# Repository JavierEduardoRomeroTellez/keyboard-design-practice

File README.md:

# keyboard-design-practice
 Practicing keyboard design

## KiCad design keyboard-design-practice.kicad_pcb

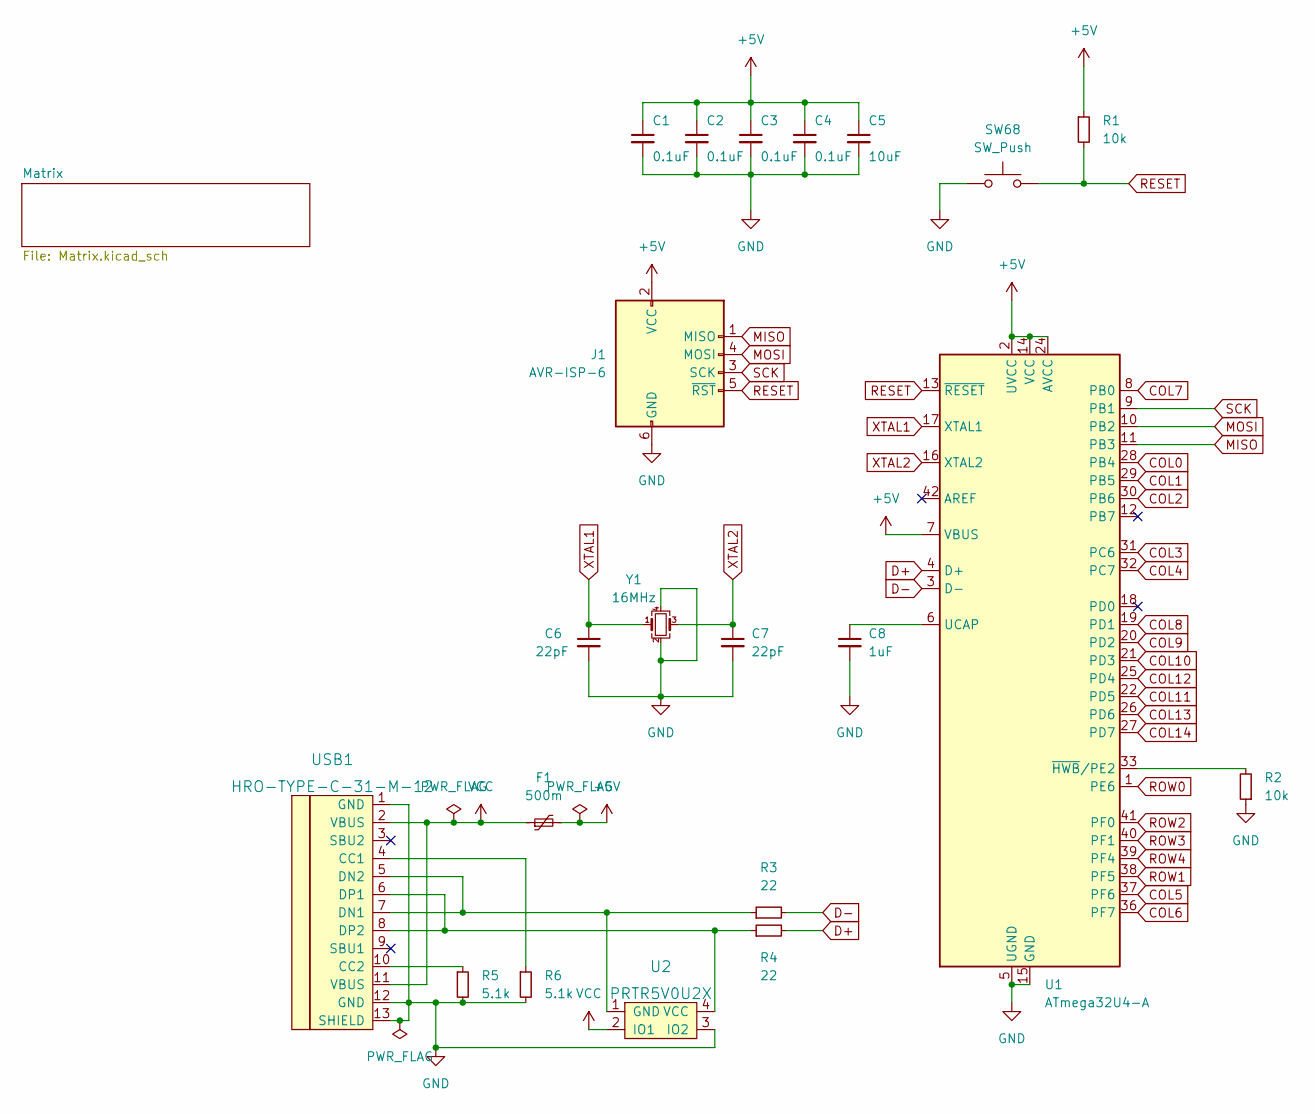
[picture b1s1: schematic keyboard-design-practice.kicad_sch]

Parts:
C1, C2, C3, C4: 0.1uF; C_0805_2012Metric_Pad1.18x1.45mm_HandSolder
C5: 10uF; C_0805_2012Metric_Pad1.18x1.45mm_HandSolder
C6, C7: 22pF; C_0805_2012Metric_Pad1.18x1.45mm_HandSolder
C8: 1uF; C_0805_2012Metric_Pad1.18x1.45mm_HandSolder
F1: 500m; Fuse_1206_3216Metric_Pad1.42x1.75mm_HandSolder
J1: AVR-ISP-6; Reset_Pretty-Mask
R1, R2: 10k; R_0805_2012Metric_Pad1.20x1.40mm_HandSolder
R3, R4: 22; R_0805_2012Metric_Pad1.20x1.40mm_HandSolder
R5, R6: 5.1k; R_0805_2012Metric_Pad1.20x1.40mm_HandSolder
SW68: SW_Push; SW_SPST_SKQG_WithStem
U1: ATmega32U4-A; TQFP-44_10x10mm_P0.8mm
U2: PRTR5V0U2X; SOT143B
USB1: HRO-TYPE-C-31-M-12; HRO-TYPE-C-31-M-12-HandSoldering
Y1: 16MHz; Crystal_SMD_3225-4Pin_3.2x2.5mm_HandSoldering

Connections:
+5V: C1.1, C2.1, C3.1, C4.1, C5.1, F1.2, J1.2 (VCC), R1.1, U1.2 (UVCC), U1.7 (VBUS), U1.14 (VCC), U1.24 (AVCC), U1.34 (VCC), U1.44 (AVCC)
COL0: U1.28 (PB4); also elsewhere on the board
COL1: U1.29 (PB5); also elsewhere on the board
COL2: U1.30 (PB6); also elsewhere on the board
COL3: U1.31 (PC6); also elsewhere on the board
COL4: U1.32 (PC7); also elsewhere on the board
COL5: U1.37 (PF6); also elsewhere on the board
COL6: U1.36 (PF7); also elsewhere on the board
COL7: U1.8 (PB0); also elsewhere on the board
COL8: U1.19 (PD1); also elsewhere on the board
COL9: U1.20 (PD2); also elsewhere on the board
COL10: U1.21 (PD3); also elsewhere on the board
COL11: U1.22 (PD5); also elsewhere on the board
COL12: U1.25 (PD4); also elsewhere on the board
COL13: U1.26 (PD6); also elsewhere on the board
COL14: U1.27 (PD7); also elsewhere on the board
D+: R4.2, U1.4 (D+)
D-: R3.2, U1.3 (D-)
GND: C1.2, C2.2, C3.2, C4.2, C5.2, C6.2, C7.2, C8.2, J1.6 (GND), R2.1, R5.2, R6.2, SW68.1, U1.5 (UGND), U1.15 (GND), U1.23 (GND), U1.35 (GND), U1.43 (GND), U2.3 (IO2), USB1.1 (GND), USB1.12 (GND), USB1.13 (SHIELD), Y1.2, Y1.4
MISO: J1.1 (MISO), U1.11 (PB3)
MOSI: J1.4 (MOSI), U1.10 (PB2)
unnamed: C8.1, U1.6 (UCAP)
unnamed: R2.2, U1.33 (~HWB/PE2)
unnamed: R3.1, U2.1 (GND), USB1.5 (DN2), USB1.7 (DN1)
unnamed: R4.1, U2.4 (VCC), USB1.6 (DP1), USB1.8 (DP2)
unnamed: R5.1, USB1.10 (CC2)
unnamed: R6.1, USB1.4 (CC1)
RESET: J1.5 (~RST), R1.2, SW68.2, U1.13 (~RESET)
ROW0: U1.1 (PE6); also elsewhere on the board
ROW1: U1.38 (PF5); also elsewhere on the board
ROW2: U1.41 (PF0); also elsewhere on the board
ROW3: U1.40 (PF1); also elsewhere on the board
ROW4: U1.39 (PF4); also elsewhere on the board
SCK: J1.3 (SCK), U1.9 (PB1)
VCC: F1.1, U2.2 (IO1), USB1.2 (VBUS), USB1.11 (VBUS)
XTAL1: C6.1, U1.17 (XTAL1), Y1.1
XTAL2: C7.1, U1.16 (XTAL2), Y1.3

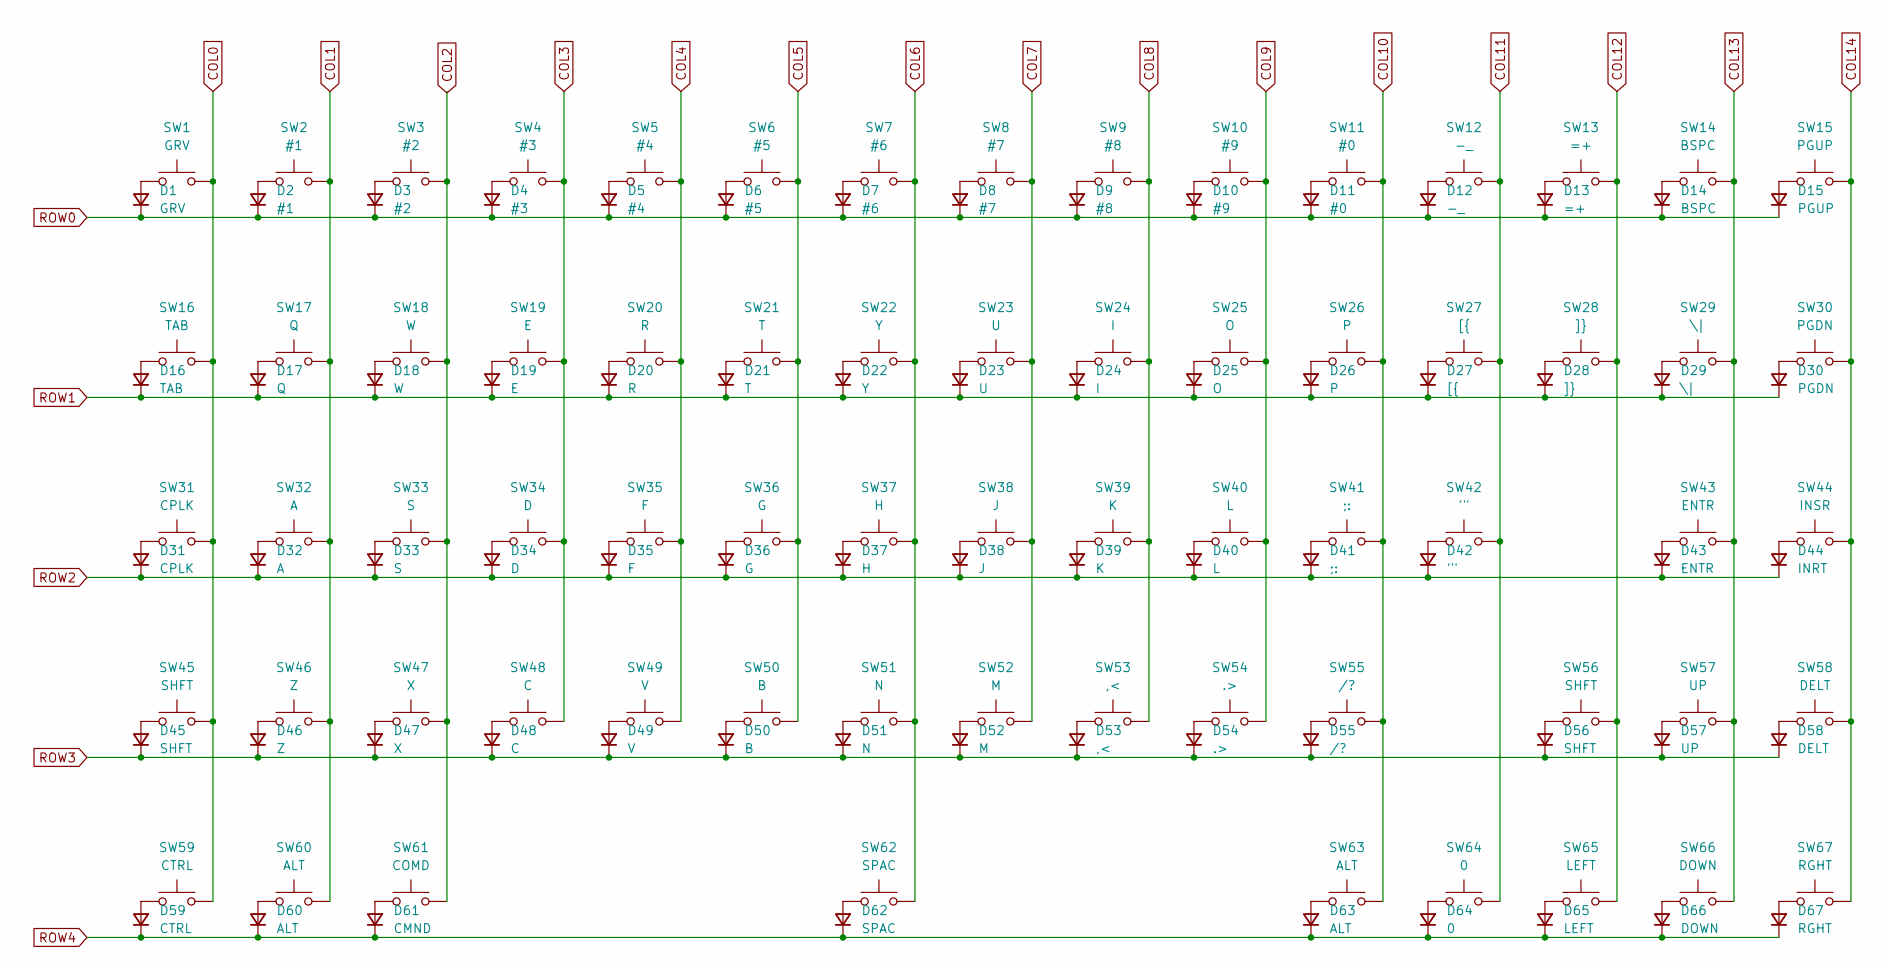
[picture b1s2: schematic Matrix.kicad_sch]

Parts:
D1: GRV; D_SOD-123
D2: #1; D_SOD-123
D3: #2; D_SOD-123
D4: #3; D_SOD-123
D5: #4; D_SOD-123
D6: #5; D_SOD-123
D7: #6; D_SOD-123
D8: #7; D_SOD-123
D9: #8; D_SOD-123
D10: #9; D_SOD-123
D11: #0; D_SOD-123
D12: -_; D_SOD-123
D13: =+; D_SOD-123
D14: BSPC; D_SOD-123
D15: PGUP; D_SOD-123
D16: TAB; D_SOD-123
D17: Q; D_SOD-123
D18: W; D_SOD-123
D19: E; D_SOD-123
D20: R; D_SOD-123
D21: T; D_SOD-123
D22: Y; D_SOD-123
D23: U; D_SOD-123
D24: I; D_SOD-123
D25: O; D_SOD-123
D26: P; D_SOD-123
D27: [{; D_SOD-123
D28: ]}; D_SOD-123
D29: \|; D_SOD-123
D30: PGDN; D_SOD-123
D31: CPLK; D_SOD-123
D32: A; D_SOD-123
D33: S; D_SOD-123
D34: D; D_SOD-123
D35: F; D_SOD-123
D36: G; D_SOD-123
D37: H; D_SOD-123
D38: J; D_SOD-123
D39: K; D_SOD-123
D40: L; D_SOD-123
D41: ;:; D_SOD-123
D42: '"; D_SOD-123
D43: ENTR; D_SOD-123
D44: INRT; D_SOD-123
D45, D56: SHFT; D_SOD-123
D46: Z; D_SOD-123
D47: X; D_SOD-123
D48: C; D_SOD-123
D49: V; D_SOD-123
D50: B; D_SOD-123
D51: N; D_SOD-123
D52: M; D_SOD-123
D53: ,<; D_SOD-123
D54: .>; D_SOD-123
D55: /?; D_SOD-123
D57: UP; D_SOD-123
D58: DELT; D_SOD-123
D59: CTRL; D_SOD-123
D60, D63: ALT; D_SOD-123
D61: CMND; D_SOD-123
D62: SPAC; D_SOD-123
D64: 0; D_SOD-123
D65: LEFT; D_SOD-123
D66: DOWN; D_SOD-123
D67: RGHT; D_SOD-123
SW1: GRV; MX-1U-NoLED
SW2: #1; MX-1U-NoLED
SW3: #2; MX-1U-NoLED
SW4: #3; MX-1U-NoLED
SW5: #4; MX-1U-NoLED
SW6: #5; MX-1U-NoLED
SW7: #6; MX-1U-NoLED
SW8: #7; MX-1U-NoLED
SW9: #8; MX-1U-NoLED
SW10: #9; MX-1U-NoLED
SW11: #0; MX-1U-NoLED
SW12: -_; MX-1U-NoLED
SW13: =+; MX-1U-NoLED
SW14: BSPC; MX-2U-NoLED
SW15: PGUP; MX-1U-NoLED
SW16: TAB; MX-1.5U-NoLED
SW17: Q; MX-1U-NoLED
SW18: W; MX-1U-NoLED
SW19: E; MX-1U-NoLED
SW20: R; MX-1U-NoLED
SW21: T; MX-1U-NoLED
SW22: Y; MX-1U-NoLED
SW23: U; MX-1U-NoLED
SW24: I; MX-1U-NoLED
SW25: O; MX-1U-NoLED
SW26: P; MX-1U-NoLED
SW27: [{; MX-1U-NoLED
SW28: ]}; MX-1U-NoLED
SW29: \|; MX-1.5U-NoLED
SW30: PGDN; MX-1U-NoLED
SW31: CPLK; MX-1.75U-NoLED
SW32: A; MX-1U-NoLED
SW33: S; MX-1U-NoLED
SW34: D; MX-1U-NoLED
SW35: F; MX-1U-NoLED
SW36: G; MX-1U-NoLED
SW37: H; MX-1U-NoLED
SW38: J; MX-1U-NoLED
SW39: K; MX-1U-NoLED
SW40: L; MX-1U-NoLED
SW41: ;:; MX-1U-NoLED
SW42: '"; MX-1U-NoLED
SW43: ENTR; MX-2.25U-NoLED
SW44: INSR; MX-1U-NoLED
SW45: SHFT; MX-2.25U-NoLED
SW46: Z; MX-1U-NoLED
SW47: X; MX-1U-NoLED
SW48: C; MX-1U-NoLED
SW49: V; MX-1U-NoLED
SW50: B; MX-1U-NoLED
SW51: N; MX-1U-NoLED
SW52: M; MX-1U-NoLED
SW53: ,<; MX-1U-NoLED
SW54: .>; MX-1U-NoLED
SW55: /?; MX-1U-NoLED
SW56: SHFT; MX-1.75U-NoLED
SW57: UP; MX-1U-NoLED
SW58: DELT; MX-1U-NoLED
SW59: CTRL; MX-1.5U-NoLED
SW60, SW63: ALT; MX-1.25U-NoLED
SW61: COMD; MX-1.5U-NoLED
SW62: SPAC; MX-6.5U-NoLED
SW64: 0; MX-1U-NoLED
SW65: LEFT; MX-1U-NoLED
SW66: DOWN; MX-1U-NoLED
SW67: RGHT; MX-1U-NoLED

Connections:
COL0: SW1.2, SW16.2, SW31.2, SW45.2, SW59.2; also elsewhere on the board
COL1: SW2.2, SW17.2, SW32.2, SW46.2, SW60.2; also elsewhere on the board
COL2: SW3.2, SW18.2, SW33.2, SW47.2, SW61.2; also elsewhere on the board
COL3: SW4.2, SW19.2, SW34.2, SW48.2; also elsewhere on the board
COL4: SW5.2, SW20.2, SW35.2, SW49.2; also elsewhere on the board
COL5: SW6.2, SW21.2, SW36.2, SW50.2; also elsewhere on the board
COL6: SW7.2, SW22.2, SW37.2, SW51.2, SW62.2; also elsewhere on the board
COL7: SW8.2, SW23.2, SW38.2, SW52.2; also elsewhere on the board
COL8: SW9.2, SW24.2, SW39.2, SW53.2; also elsewhere on the board
COL9: SW10.2, SW25.2, SW40.2, SW54.2; also elsewhere on the board
COL10: SW11.2, SW26.2, SW41.2, SW55.2, SW63.2; also elsewhere on the board
COL11: SW12.2, SW27.2, SW42.2, SW64.2; also elsewhere on the board
COL12: SW13.2, SW28.2, SW56.2, SW65.2; also elsewhere on the board
COL13: SW14.2, SW29.2, SW43.2, SW57.2, SW66.2; also elsewhere on the board
COL14: SW15.2, SW30.2, SW44.2, SW58.2, SW67.2; also elsewhere on the board
unnamed: D1.2 (A), SW1.1
unnamed: D2.2 (A), SW2.1
unnamed: D3.2 (A), SW3.1
unnamed: D4.2 (A), SW4.1
unnamed: D5.2 (A), SW5.1
unnamed: D6.2 (A), SW6.1
unnamed: D7.2 (A), SW7.1
unnamed: D8.2 (A), SW8.1
unnamed: D9.2 (A), SW9.1
unnamed: D10.2 (A), SW10.1
unnamed: D11.2 (A), SW11.1
unnamed: D12.2 (A), SW12.1
unnamed: D13.2 (A), SW13.1
unnamed: D14.2 (A), SW14.1
unnamed: D15.2 (A), SW15.1
unnamed: D16.2 (A), SW16.1
unnamed: D17.2 (A), SW17.1
unnamed: D18.2 (A), SW18.1
unnamed: D19.2 (A), SW19.1
unnamed: D20.2 (A), SW20.1
unnamed: D21.2 (A), SW21.1
unnamed: D22.2 (A), SW22.1
unnamed: D23.2 (A), SW23.1
unnamed: D24.2 (A), SW24.1
unnamed: D25.2 (A), SW25.1
unnamed: D26.2 (A), SW26.1
unnamed: D27.2 (A), SW27.1
unnamed: D28.2 (A), SW28.1
unnamed: D29.2 (A), SW29.1
unnamed: D30.2 (A), SW30.1
unnamed: D31.2 (A), SW31.1
unnamed: D32.2 (A), SW32.1
unnamed: D33.2 (A), SW33.1
unnamed: D34.2 (A), SW34.1
unnamed: D35.2 (A), SW35.1
unnamed: D36.2 (A), SW36.1
unnamed: D37.2 (A), SW37.1
unnamed: D38.2 (A), SW38.1
unnamed: D39.2 (A), SW39.1
unnamed: D40.2 (A), SW40.1
unnamed: D41.2 (A), SW41.1
unnamed: D42.2 (A), SW42.1
unnamed: D43.2 (A), SW43.1
unnamed: D44.2 (A), SW44.1
unnamed: D45.2 (A), SW45.1
unnamed: D46.2 (A), SW46.1
unnamed: D47.2 (A), SW47.1
unnamed: D48.2 (A), SW48.1
unnamed: D49.2 (A), SW49.1
unnamed: D50.2 (A), SW50.1
unnamed: D51.2 (A), SW51.1
unnamed: D52.2 (A), SW52.1
unnamed: D53.2 (A), SW53.1
unnamed: D54.2 (A), SW54.1
unnamed: D55.2 (A), SW55.1
unnamed: D56.2 (A), SW56.1
unnamed: D57.2 (A), SW57.1
unnamed: D58.2 (A), SW58.1
unnamed: D59.2 (A), SW59.1
unnamed: D60.2 (A), SW60.1
unnamed: D61.2 (A), SW61.1
unnamed: D62.2 (A), SW62.1
unnamed: D63.2 (A), SW63.1
unnamed: D64.2 (A), SW64.1
unnamed: D65.2 (A), SW65.1
unnamed: D66.2 (A), SW66.1
unnamed: D67.2 (A), SW67.1
ROW0: D1.1 (K), D2.1 (K), D3.1 (K), D4.1 (K), D5.1 (K), D6.1 (K), D7.1 (K), D8.1 (K), D9.1 (K), D10.1 (K), D11.1 (K), D12.1 (K), D13.1 (K), D14.1 (K), D15.1 (K); also elsewhere on the board
ROW1: D16.1 (K), D17.1 (K), D18.1 (K), D19.1 (K), D20.1 (K), D21.1 (K), D22.1 (K), D23.1 (K), D24.1 (K), D25.1 (K), D26.1 (K), D27.1 (K), D28.1 (K), D29.1 (K), D30.1 (K); also elsewhere on the board
ROW2: D31.1 (K), D32.1 (K), D33.1 (K), D34.1 (K), D35.1 (K), D36.1 (K), D37.1 (K), D38.1 (K), D39.1 (K), D40.1 (K), D41.1 (K), D42.1 (K), D43.1 (K), D44.1 (K); also elsewhere on the board
ROW3: D45.1 (K), D46.1 (K), D47.1 (K), D48.1 (K), D49.1 (K), D50.1 (K), D51.1 (K), D52.1 (K), D53.1 (K), D54.1 (K), D55.1 (K), D56.1 (K), D57.1 (K), D58.1 (K); also elsewhere on the board
ROW4: D59.1 (K), D60.1 (K), D61.1 (K), D62.1 (K), D63.1 (K), D64.1 (K), D65.1 (K), D66.1 (K), D67.1 (K); also elsewhere on the board

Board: 2 copper layers, 155 parts (89 on the bottom side), 104 nets, no tracks yet.

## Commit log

2022-05-14 created kicad project
2022-05-14 Add submodules
2022-05-14 Added symbols and footprints
2022-05-14 Finished the MCU setting
2022-05-15 Created the key matrix
2022-05-15 Assigned the columns and rows to the MCU
2022-05-15 ERC done
2022-05-15 Schema finished
2022-05-15 Diodes & switches footprints in place
2022-05-15 All footprints in place
2022-05-15 little changes
2022-05-16 Finished pcb design
